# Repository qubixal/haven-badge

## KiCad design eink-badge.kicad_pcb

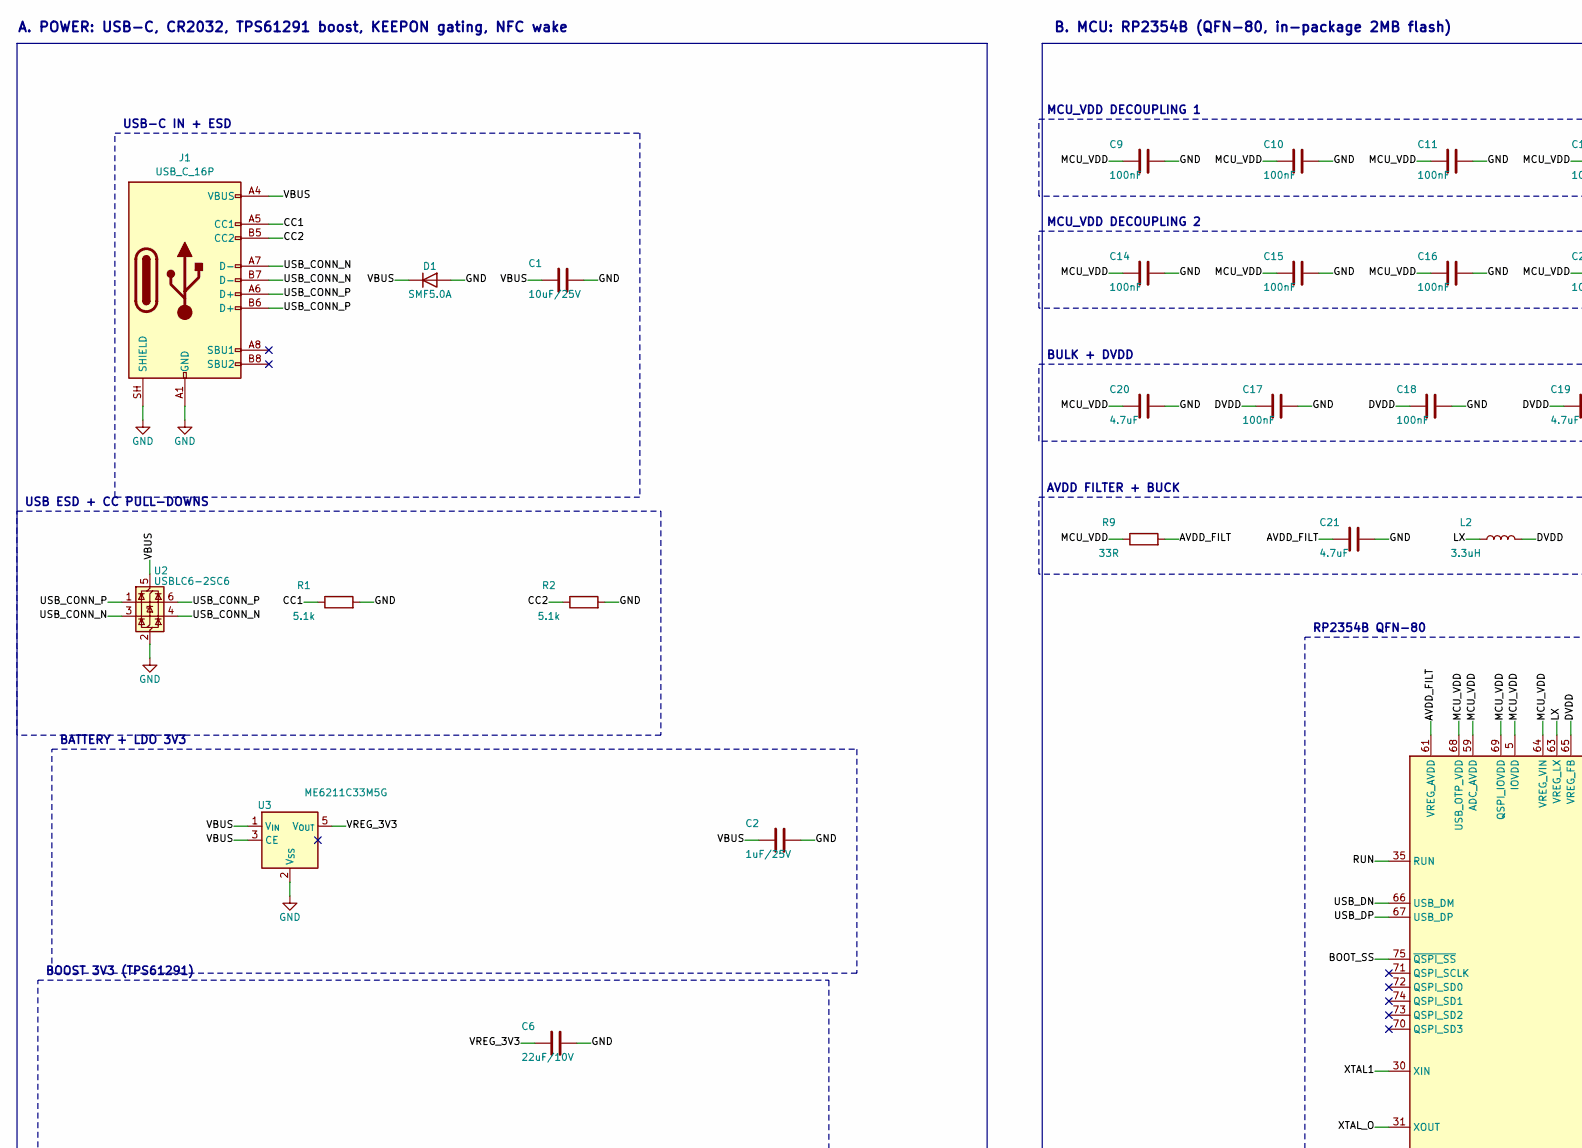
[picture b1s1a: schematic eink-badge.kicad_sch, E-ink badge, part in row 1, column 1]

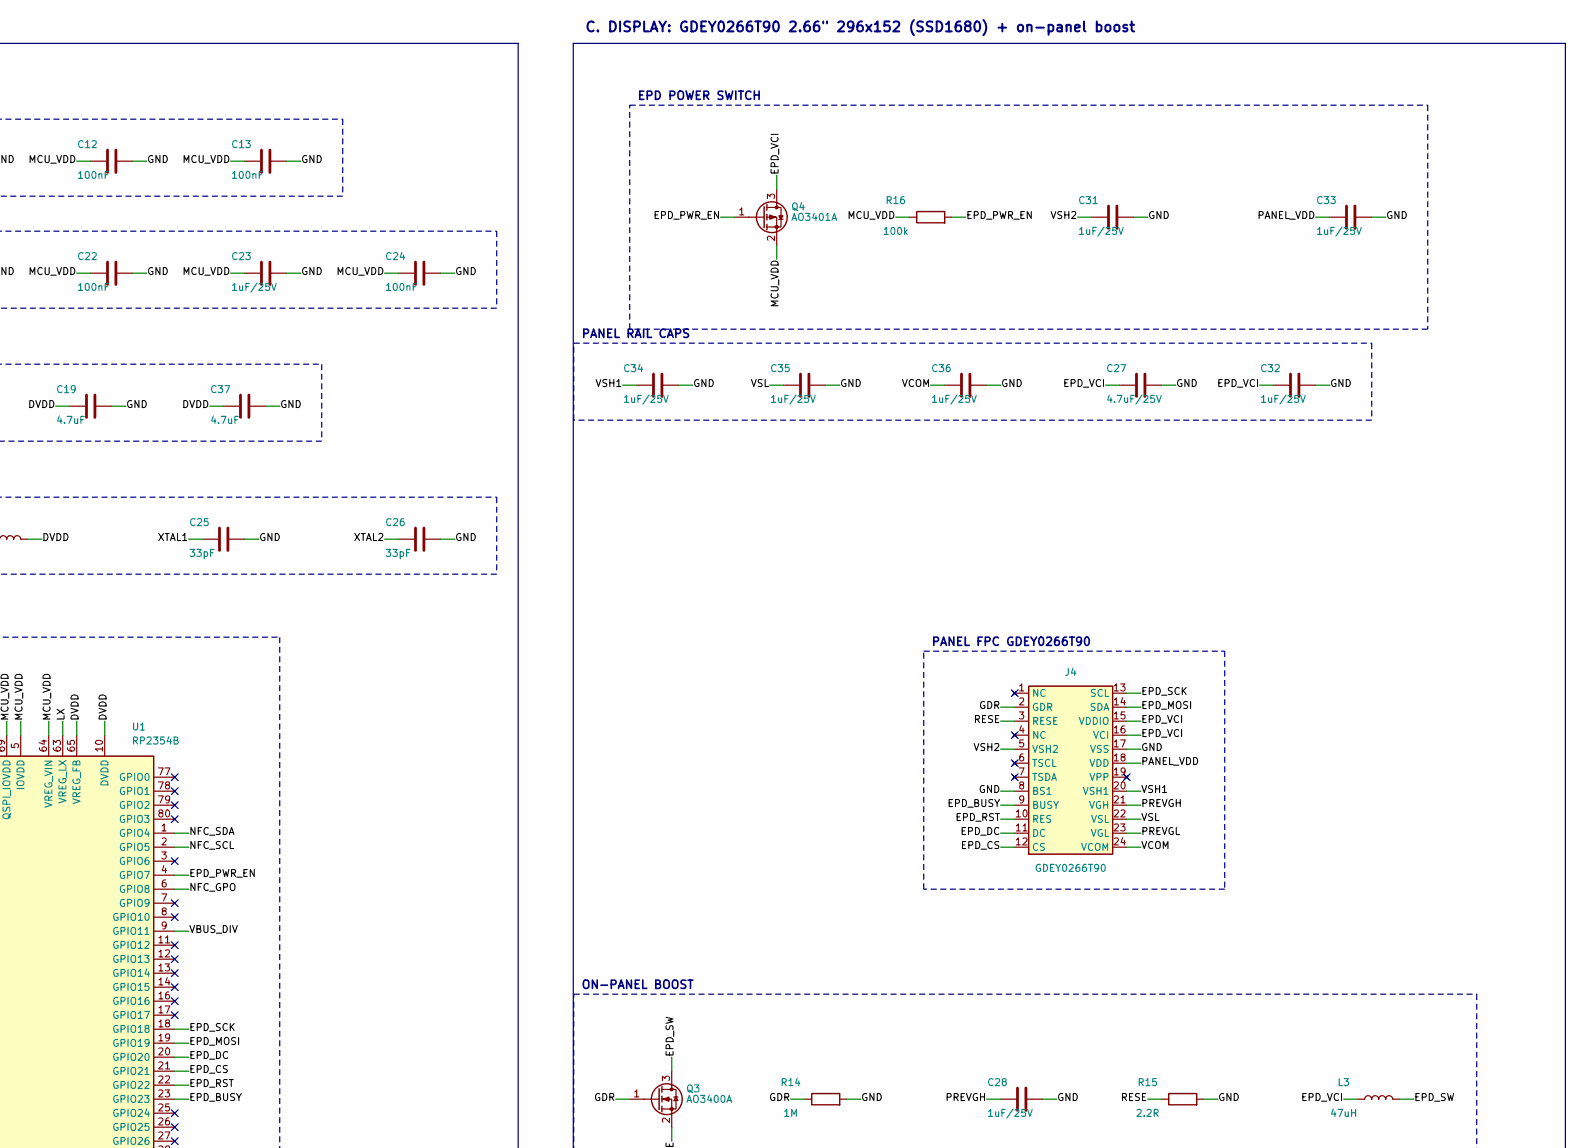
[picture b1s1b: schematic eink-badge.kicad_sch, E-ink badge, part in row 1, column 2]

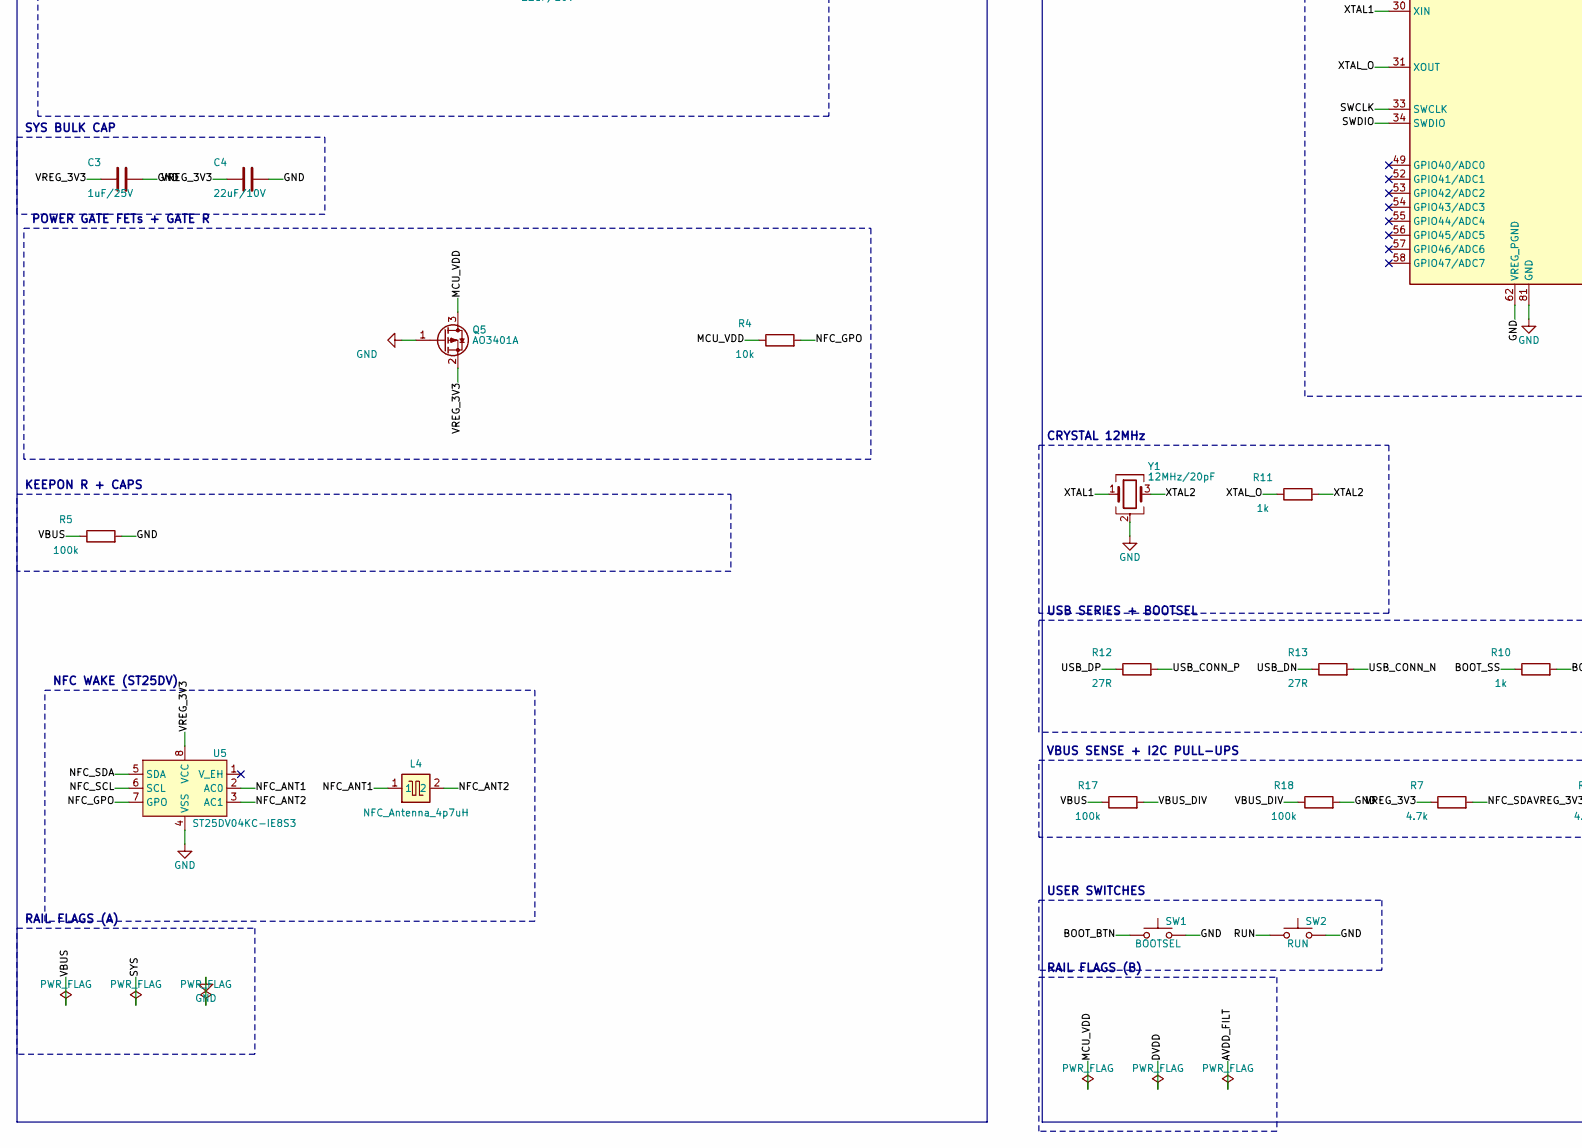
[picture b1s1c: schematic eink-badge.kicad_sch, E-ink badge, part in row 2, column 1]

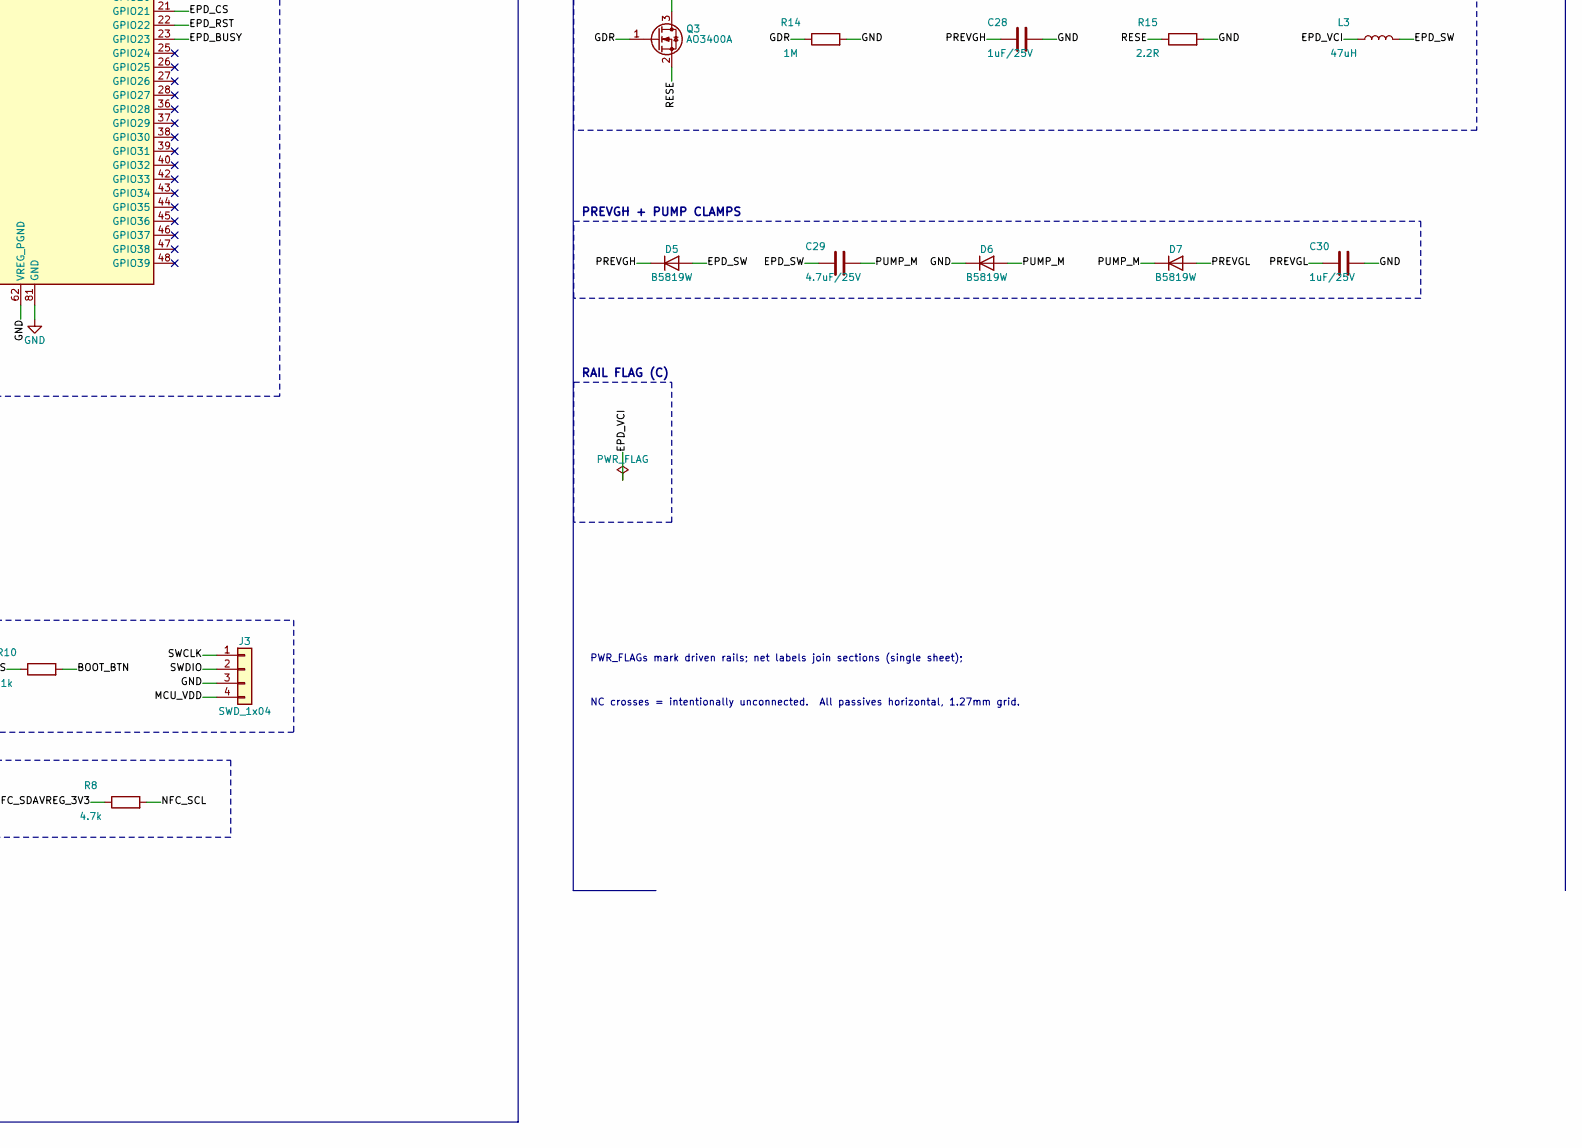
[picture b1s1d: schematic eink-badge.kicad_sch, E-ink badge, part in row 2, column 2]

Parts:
C1: 10uF/25V; C_0805_2012Metric
C2, C3, C23, C31, C32, C33, C34, C35, C36: 1uF/25V; C_0603_1608Metric
C4, C6: 22uF/10V; C_0805_2012Metric
C9, C10, C11, C12, C13, C14, C15, C16, C17, C18, C22, C24: 100nF; C_0402_1005Metric
C19, C20, C21, C37: 4.7uF; C_0603_1608Metric
C25, C26: 33pF; C_0402_1005Metric
C27, C29: 4.7uF/25V; C_0805_2012Metric
C28, C30: 1uF/25V; C_0805_2012Metric
D1: SMF5.0A; D_SOD-123F
D5, D6, D7: B5819W; D_SOD-123
J1: USB_C_16P; USB_C_Receptacle_HRO_TYPE-C-31-M-12
J3: SWD_1x04; SWD_4p_SMD_P2.54mm
J4: GDEY0266T90; Jushuo_AFC07-S24FCA-00_1x24-1MP_P0.50_Horizontal
L2: 3.3uH; L_Changjiang_FNR3015S
L3: 47uH; L_Changjiang_FNR3015S
L4: NFC_Antenna_4p7uH
Q3: AO3400A; SOT-23
Q4, Q5: AO3401A; SOT-23
R1, R2: 5.1k; R_0402_1005Metric
R4: 10k; R_0402_1005Metric
R5, R16, R17, R18: 100k; R_0402_1005Metric
R7, R8: 4.7k; R_0402_1005Metric
R9: 33R; R_0402_1005Metric
R10, R11: 1k; R_0402_1005Metric
R12, R13: 27R; R_0402_1005Metric
R14: 1M; R_0402_1005Metric
R15: 2.2R; R_0402_1005Metric
SW1: BOOTSEL; SW_TS1187A_2pad
SW2: RUN; SW_TS1187A_2pad
U1: RP2354B; QFN-80-1EP_10x10mm_P0.4mm_EP3.4x3.4mm
U2: USBLC6-2SC6; SOT-23-6
U3: ME6211C33M5G; SOT-23-5
U5: ST25DV04KC-IE8S3; SOIC-8_3.9x4.9mm_P1.27mm
Y1: 12MHz/20pF; Crystal_SMD_3225-4Pin_3.2x2.5mm

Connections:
/AVDD_FILT: C21.1, R9.2, U1.61 (VREG_AVDD)
/BOOT_BTN: R10.2, SW1.1
/BOOT_SS: R10.1, U1.75 (~QSPI_SS)
/CC1: J1.A5 (CC1), R1.1
/CC2: J1.B5 (CC2), R2.1
/EPD_BUSY: J4.9 (BUSY), U1.23 (GPIO23)
/EPD_CS: J4.12 (CS), U1.21 (GPIO21)
/EPD_DC: J4.11 (DC), U1.20 (GPIO20)
/EPD_MOSI: J4.14 (SDA), U1.19 (GPIO19)
/EPD_PWR_EN: Q4.1 (G), R16.2, U1.4 (GPIO7)
/EPD_RST: J4.10 (RES), U1.22 (GPIO22)
/EPD_SCK: J4.13 (SCL), U1.18 (GPIO18)
/EPD_SW: C29.1, D5.2 (A), L3.2, Q3.3 (D)
/EPD_VCI: C27.1, C32.1, J4.15 (VDDIO), J4.16 (VCI), L3.1, Q4.3 (D)
/GDR: J4.2 (GDR), Q3.1 (G), R14.1
/LX: L2.1, U1.63 (VREG_LX)
/MCU_VDD: C9.1, C10.1, C11.1, C12.1, C13.1, C14.1, C15.1, C16.1, C20.1, C22.1, C23.1, C24.1, J3.4, Q4.2 (S), Q5.3 (D), R4.1, R9.1, R16.1, U1.5 (IOVDD), U1.15 (IOVDD), U1.24 (IOVDD), U1.29 (IOVDD), U1.41 (IOVDD), U1.50 (IOVDD), U1.59 (ADC_AVDD), U1.60 (IOVDD), U1.64 (VREG_VIN), U1.68 (USB_OTP_VDD), U1.69 (QSPI_IOVDD), U1.76 (IOVDD)
/NFC_ANT1: L4.1, U5.2 (AC0)
/NFC_ANT2: L4.2, U5.3 (AC1)
/NFC_GPO: R4.2, U1.6 (GPIO8), U5.7 (GPO)
/NFC_SCL: R8.2, U1.2 (GPIO5), U5.6 (SCL)
/NFC_SDA: R7.2, U1.1 (GPIO4), U5.5 (SDA)
/PANEL_VDD: C33.1, J4.18 (VDD)
/PREVGH: C28.1, D5.1 (K), J4.21 (VGH)
/PREVGL: C30.1, D7.2 (A), J4.23 (VGL)
/PUMP_M: C29.2, D6.2 (A), D7.1 (K)
/RESE: J4.3 (RESE), Q3.2 (S), R15.1
/RUN: SW2.1, U1.35 (RUN)
/SWCLK: J3.1, U1.33 (SWCLK)
/SWDIO: J3.2, U1.34 (SWDIO)
/USB_CONN_N: J1.A7 (D-), J1.B7 (D-), R13.2, U2.3 (I/O2), U2.4 (I/O2)
/USB_CONN_P: J1.A6 (D+), J1.B6 (D+), R12.2, U2.1 (I/O1), U2.6 (I/O1)
/USB_DN: R13.1, U1.66 (USB_DM)
/USB_DP: R12.1, U1.67 (USB_DP)
/VBUS: C1.1, C2.1, D1.1 (K), J1.A4 (VBUS), J1.A9 (VBUS), J1.B4 (VBUS), J1.B9 (VBUS), R5.1, R17.1, U2.5 (VBUS), U3.1 (V_{IN}), U3.3 (CE)
/VBUS_DIV: R17.2, R18.1, U1.9 (GPIO11)
/VCOM: C36.1, J4.24 (VCOM)
/VREG_3V3: C3.1, C4.1, C6.1, Q5.2 (S), R7.1, R8.1, U3.5 (V_{OUT}), U5.8 (VCC)
/VSH1: C34.1, J4.20 (VSH1)
/VSH2: C31.1, J4.5 (VSH2)
/VSL: C35.1, J4.22 (VSL)
/XTAL1: C25.1, U1.30 (XIN), Y1.1
/XTAL2: C26.1, R11.2, Y1.3
/XTAL_O: R11.1, U1.31 (XOUT)

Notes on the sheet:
A. POWER: USB-C, CR2032, TPS61291 boost, KEEPON gating, NFC wake
B. MCU: RP2354B (QFN-80, in-package 2MB flash)
C. DISPLAY: GDEY0266T90 2.66" 296x152 (SSD1680) + on-panel boost
USB-C IN + ESD
USB ESD + CC PULL-DOWNS
BATTERY + LDO 3V3
BOOST 3V3 (TPS61291)
SYS BULK CAP
POWER GATE FETs + GATE R
KEEPON R + CAPS
NFC WAKE (ST25DV)
RAIL FLAGS (A)
MCU_VDD DECOUPLING 1
MCU_VDD DECOUPLING 2
BULK + DVDD
AVDD FILTER + BUCK
RP2354B QFN-80
CRYSTAL 12MHz
USB SERIES + BOOTSEL
VBUS SENSE + I2C PULL-UPS
USER SWITCHES
RAIL FLAGS (B)
EPD POWER SWITCH
PANEL RAIL CAPS
PANEL FPC GDEY0266T90
ON-PANEL BOOST
PREVGH + PUMP CLAMPS
RAIL FLAG (C)
PWR_FLAGs mark driven rails; net labels join sections (single sheet);
NC crosses = intentionally unconnected. All passives horizontal, 1.27mm grid.

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
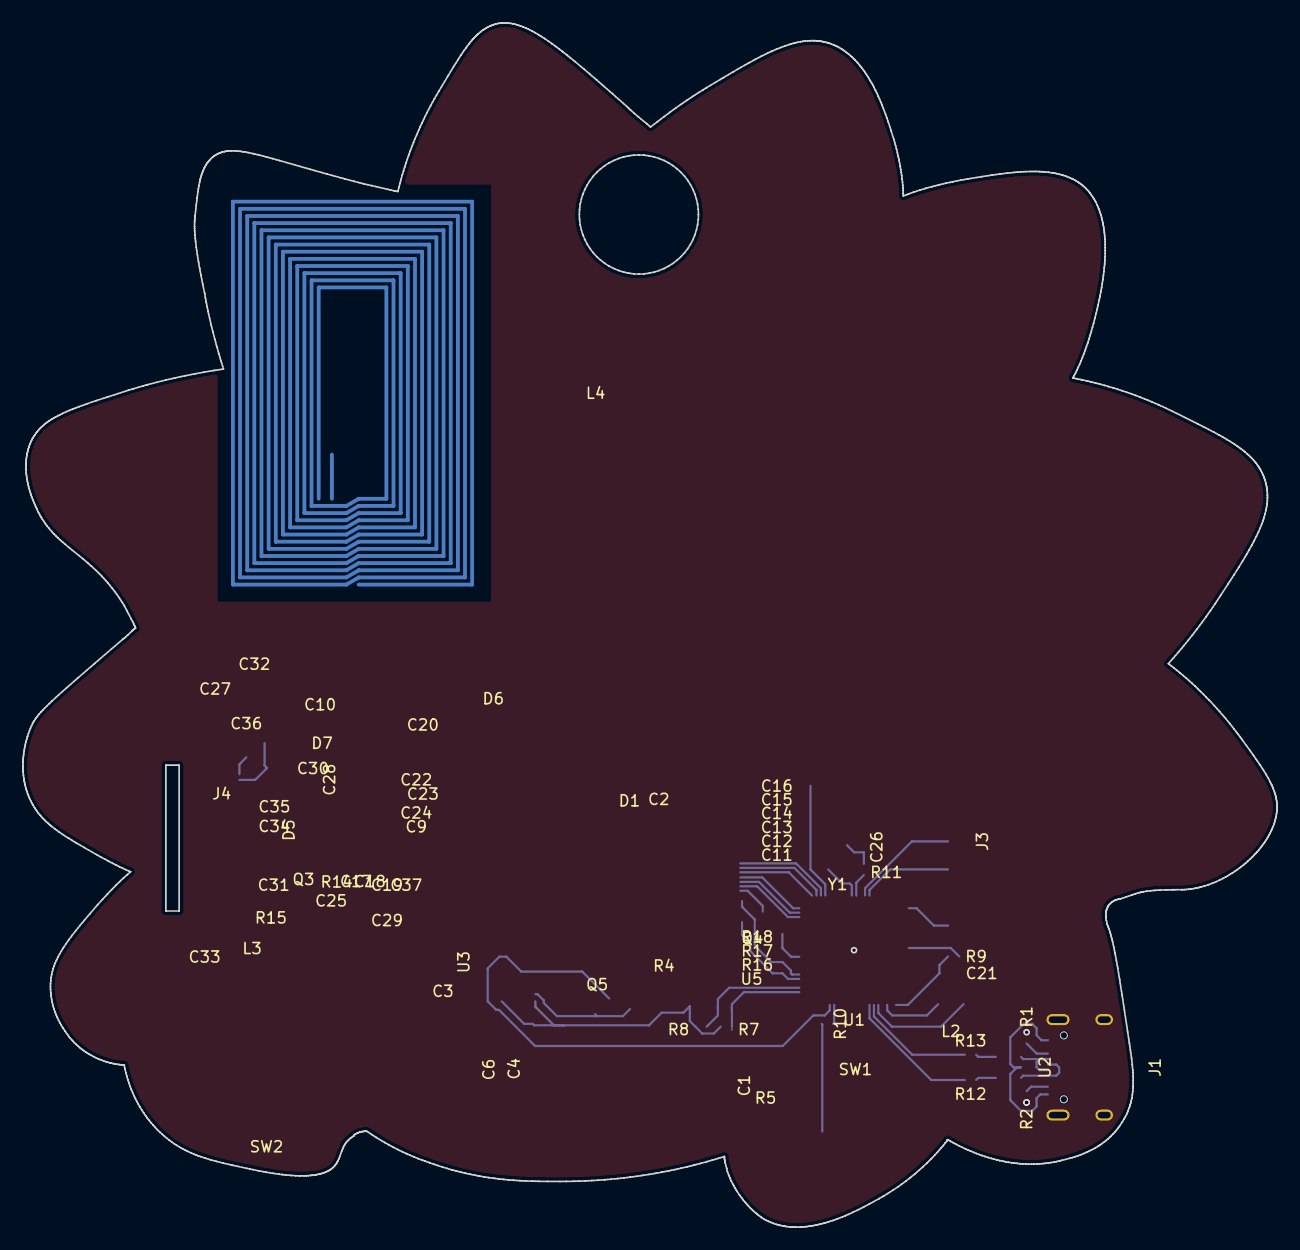
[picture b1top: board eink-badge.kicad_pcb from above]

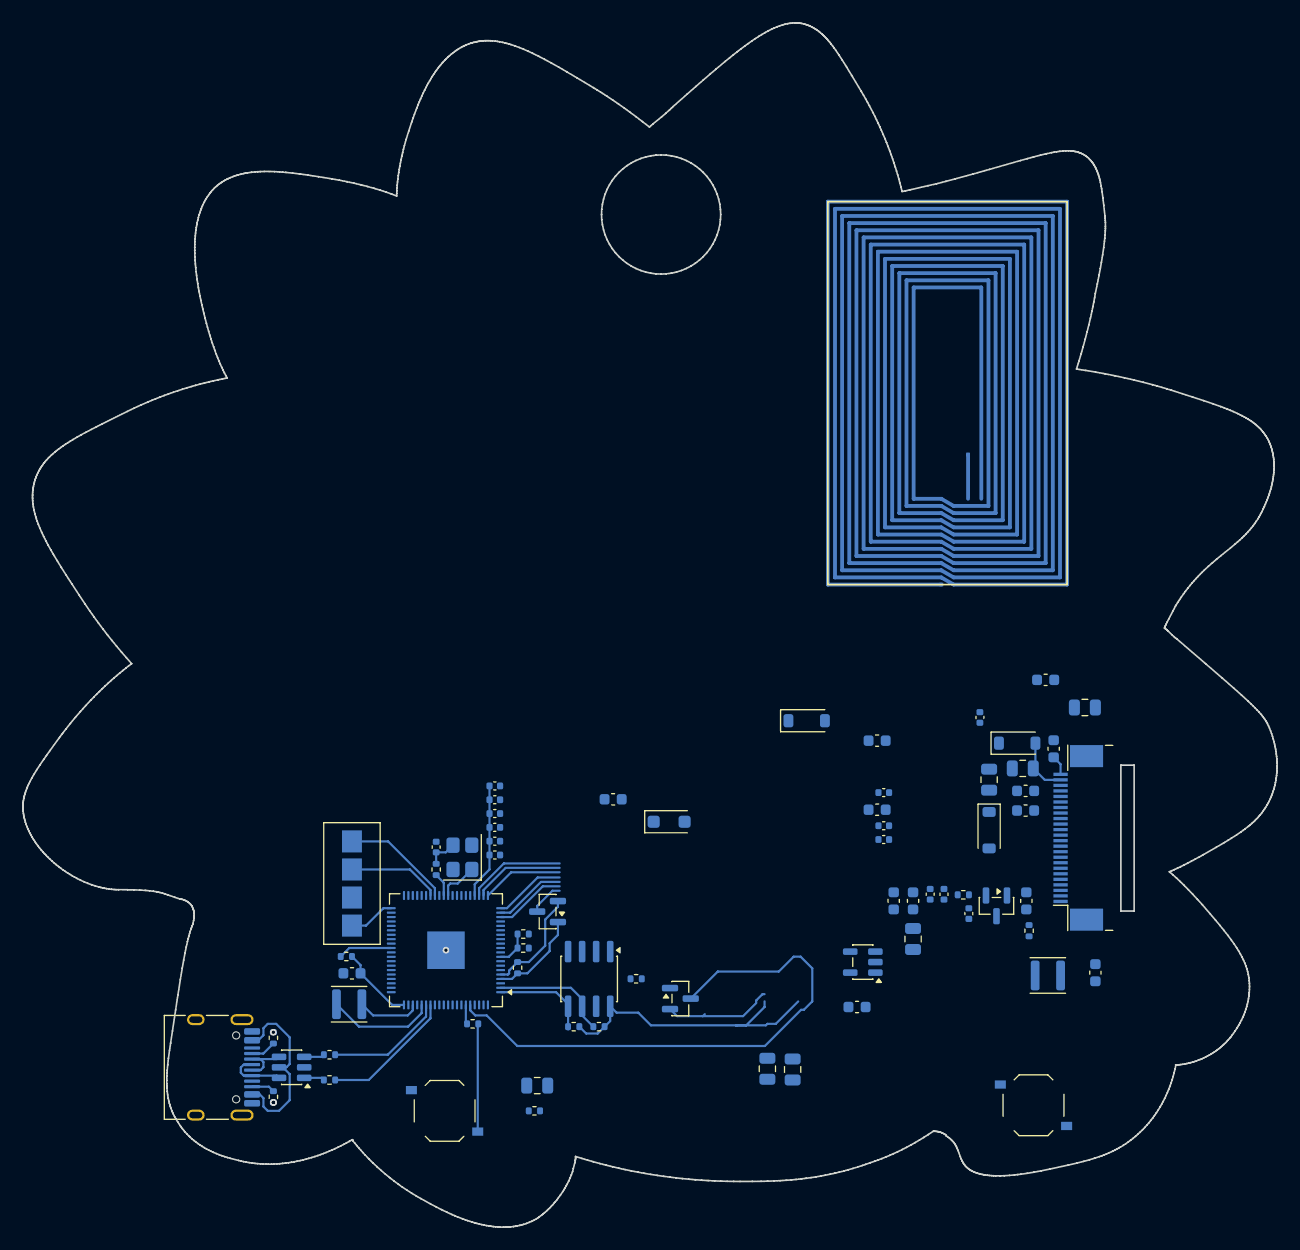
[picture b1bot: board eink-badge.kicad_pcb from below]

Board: 2 copper layers, 113.5 x 109.0 mm, 70 parts (70 on the bottom side), 46 nets.
